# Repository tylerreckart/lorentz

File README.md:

# LORENTZ
An all-analog topology complex oscillator inspired by Don Buchla’s 259. Sized for Eurorack (28 HP).  

![LORENTZ REV-A front panels, off-white and black][image-1]

## Overview
Two oscillators, a modulation oscillator and a principal oscillator:
- **Modulation oscillator:** coarse dial (about 0.1 Hz to 1.6 kHz; the -3 to +3 engraving is a set of landmarks), FREQ CV input, MOD OUTS (two waveforms).
- **Principal oscillator:** coarse tuning dial (-3 to +3 octaves), FINE, PITCH (1 V/oct) and EXP CV inputs, PRINC OUTS (two waveforms).
- **Modulation:** INDEX and AM, with an EXP/LIN toggle.
- **Timbre:** TIMBRE (wavefolder) and SYMM, with the FINAL output.
- **Waveshaping:** SHAPE (triangle to square), with a WAVE output.

Full operating and calibration instructions are in the [manual](MANUAL.md) ([PDF](docs/LORENTZ_REV-A_Manual.pdf)).
## Front panel
- Eurorack 3U x 28 HP: **141.9 x 128.5 mm**, square corners.
- **2.0 mm** 5052 (or 6061) aluminium.
- **39 holes + 4 rail slots.**

| Feature         | Qty | Dia (mm)                                 | Part                                   |
| --------------- | --- | ---------------------------------------- | -------------------------------------- |
| Pot bushings    | 8   | 7.3                                      | Alpha 9 mm x6, Alpha RV16 x2 (M7x0.75) |
| Jacks           | 13  | 6.3                                      | Thonkiconn PJ398SM (M6)                |
| Toggle          | 1   | 5.2                                      | Dailywell 2MD1T1B1M2QES (10-48 UNS)    |
| LEDs            | 11  | 3.2                                      | 3 mm LED, lens flush (9 red, 2 amber)  |
| Standoff screws | 6   | 3.4 thru + 90° countersink Ø6.0 on front | M3x6 DIN 965 / ISO 7046 countersunk    |
| Rail slots      | 4   | 5.6 x 3.2 stadium                        | M3 rail screws                         |

Colourways:

| Version   | Base           | Ink                 | Accents                    |
| --------- | -------------- | ------------------- | -------------------------- |
| Off-white | \#E9E6DC matte | \#2A1404 dark brown | red #D8302A, amber #ECB731 |
| Black     | \#2C2C2C matte | white               | red #D8302A, amber #ECB731 |

Full details, including countersink depth and print registration, are in `panel/<colour>/PANEL_FAB_SPEC.md`.
## Fabrication
**PCBs.** Zip and upload each gerber folder separately:
- `control_board/gerbers/` (12 files: 4 copper, mask, silk, edge, drill + map, job)
- `circuit_board/gerbers/` (same)
**Panel.**
1. Cut and drill from `panel/<colour>/panel_REV-A_cut.dxf` (mm, origin bottom-left; layers `CUT` and `CSK_FRONT_6.0x90`). `panel_REV-A_cut.svg` is the same geometry.
2. Countersink the six standoff holes first, then UV-print.
3. Print from `panel/<colour>/LORENTZ_REV-A_print_<colour>_outlined.svg`. Register to the hole centers in `panel_REV-A_holes.csv` within ±0.2 mm.
Ask the fab for a color proof against the base color.
## Bill of materials
See `bom/`. `LORENTZ_REV-A_BOM.csv` lists suppliers, part numbers and prices (`need` is the count for one build; `qty` includes spares). The `*_bom_from_sch.csv` files are fresh exports from the schematics.
## Calibration
There are three trimmers on the rear of the circuit board: RV4 (1 V/oct scale), RV5 (high-frequency tracking) and RV11 (SHAPE CV offset null). See section 12 of the [manual](MANUAL.md).
## Repository layout
- `MANUAL.md`: user manual (source). `docs/LORENTZ_REV-A_Manual.pdf` is the printable version; `images/manual/` holds its figures.
- `control_board/`, `circuit_board/`: KiCad projects, schematic PDFs, pick-and-place files and `gerbers/`.
- `panel/<colour>/`: panel cut files, print artwork and `PANEL_FAB_SPEC.md`.
- `bom/`: bills of materials.
- `images/`: panel renders.
## License
Apache 2.0

[image-1]:	images/LORENTZ_REV-A_offwhite.png

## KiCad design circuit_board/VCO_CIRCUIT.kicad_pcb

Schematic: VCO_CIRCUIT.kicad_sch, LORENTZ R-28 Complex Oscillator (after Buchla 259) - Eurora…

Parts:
C1, C2: 47u; CP_Radial_D5.0mm_P2.00mm
C3, C4, C6, C7, C8, C9, C10, C11, C12, C13, C17, C18, C19, C20, C23, C24, C26, C27, C28, C29, C30, C31, C36, C37, C38, C39, C44, C45, C46, C47, C48, C49: 100n; C_Disc_D3.0mm_W2.0mm_P2.50mm
C5: 10u; CP_Radial_D5.0mm_P2.00mm
C14, C21, C33, C35, C41, C43: 47p; C_Disc_D3.0mm_W2.0mm_P2.50mm
C15, C22, C32, C34, C40, C42: 100p; C_Disc_D3.0mm_W2.0mm_P2.50mm
C16: 10n C0G; C_Disc_D3.0mm_W2.0mm_P2.50mm
C25: 330p C0G; C_Disc_D3.0mm_W2.0mm_P2.50mm
D1, D2: 1N5817; D_DO-41_SOD81_P10.16mm_Horizontal
D3: BZX79C5V1; D_DO-35_SOD27_P2.54mm_Vertical_KathodeUp
D4, D5, D6, D7, D8, D9, D10, D11, D12, D13, D14, D15, D16, D17, D18, D19, D20, D21, D22, D24, D26, D28, D30, D32, D34, D36, D38, D42: 1N4148; D_DO-35_SOD27_P2.54mm_Vertical_KathodeUp
D45: BZX79B6V8; D_DO-35_SOD27_P2.54mm_Vertical_KathodeUp
J1: Eurorack 10p; IDC-Header_2x05_P2.54mm_Vertical__J1
J20, J21: B2B 2x15 female; PinSocket_2x15_P2.54mm_Vertical
Q1, Q2, Q3, Q4: BC557B; TO-92_Inline
R1, R2: 10; R_Axial_DIN0204_L3.6mm_D1.6mm_P2.54mm_Vertical
R3, R21, R41, R43, R44, R46, R50, R119, R120, R121, R122, R123, R124, R125, R126, R128: 2.2k; R_Axial_DIN0204_L3.6mm_D1.6mm_P2.54mm_Vertical
R4: 187k; R_Axial_DIN0204_L3.6mm_D1.6mm_P2.54mm_Vertical
R5, R31, R32: 110k; R_Axial_DIN0204_L3.6mm_D1.6mm_P2.54mm_Vertical
R6, R33: 2k +3300ppm; R_Axial_DIN0204_L3.6mm_D1.6mm_P2.54mm_Vertical
R7, R34: 47; R_Axial_DIN0204_L3.6mm_D1.6mm_P2.54mm_Vertical
R8: 3.92Meg; R_Axial_DIN0204_L3.6mm_D1.6mm_P2.54mm_Vertical
R9, R36: 6.8k; R_Axial_DIN0204_L3.6mm_D1.6mm_P2.54mm_Vertical
R10: 4.7Meg; R_Axial_DIN0204_L3.6mm_D1.6mm_P2.54mm_Vertical
R12, R13, R67, R68, R78, R79, R95, R96, R110, R111: 220; R_Axial_DIN0204_L3.6mm_D1.6mm_P2.54mm_Vertical
R14, R129, R130: 4.7k; R_Axial_DIN0204_L3.6mm_D1.6mm_P2.54mm_Vertical
R15, R17, R24, R25, R45, R47, R64, R65, R104, R118: 1k; R_Axial_DIN0204_L3.6mm_D1.6mm_P2.54mm_Vertical
R16, R18: 470; R_Axial_DIN0204_L3.6mm_D1.6mm_P2.54mm_Vertical
R19, R48: 47k; R_Axial_DIN0204_L3.6mm_D1.6mm_P2.54mm_Vertical
R20, R74, R103: 30k; R_Axial_DIN0204_L3.6mm_D1.6mm_P2.54mm_Vertical
R22, R60: 5.1k; R_Axial_DIN0204_L3.6mm_D1.6mm_P2.54mm_Vertical
R23, R38, R52, R55, R56, R57, R59, R61, R62, R63, R72, R84, R88, R89, R90, R91, R92, R93, R101, R105, R107, R114: 10k; R_Axial_DIN0204_L3.6mm_D1.6mm_P2.54mm_Vertical
R26: 442k; R_Axial_DIN0204_L3.6mm_D1.6mm_P2.54mm_Vertical
R27, R28: 220k; R_Axial_DIN0204_L3.6mm_D1.6mm_P2.54mm_Vertical
R29: 3.3Meg; R_Axial_DIN0204_L3.6mm_D1.6mm_P2.54mm_Vertical
R30, R71, R73, R75, R76, R83, R85, R94, R98, R100, R102, R109, R113, R115, R117, R131: 100k; R_Axial_DIN0204_L3.6mm_D1.6mm_P2.54mm_Vertical
R35: 1.5Meg; R_Axial_DIN0204_L3.6mm_D1.6mm_P2.54mm_Vertical
R37: 1Meg; R_Axial_DIN0204_L3.6mm_D1.6mm_P2.54mm_Vertical
R39: 22k; R_Axial_DIN0204_L3.6mm_D1.6mm_P2.54mm_Vertical
R40, R42: 18k; R_Axial_DIN0204_L3.6mm_D1.6mm_P2.54mm_Vertical
R49, R66, R77: 68k; R_Axial_DIN0204_L3.6mm_D1.6mm_P2.54mm_Vertical
R51: 4.3k; R_Axial_DIN0204_L3.6mm_D1.6mm_P2.54mm_Vertical
R53: 91k; R_Axial_DIN0204_L3.6mm_D1.6mm_P2.54mm_Vertical
R54: 39k; R_Axial_DIN0204_L3.6mm_D1.6mm_P2.54mm_Vertical
R58: 20k; R_Axial_DIN0204_L3.6mm_D1.6mm_P2.54mm_Vertical
R69, R80, R99: 200k; R_Axial_DIN0204_L3.6mm_D1.6mm_P2.54mm_Vertical
R70, R81: 330k; R_Axial_DIN0204_L3.6mm_D1.6mm_P2.54mm_Vertical
R82: 680k; R_Axial_DIN0204_L3.6mm_D1.6mm_P2.54mm_Vertical
R86, R133: 470k; R_Axial_DIN0204_L3.6mm_D1.6mm_P2.54mm_Vertical
R87: 25.5k; R_Axial_DIN0204_L3.6mm_D1.6mm_P2.54mm_Vertical
R97: 240k; R_Axial_DIN0204_L3.6mm_D1.6mm_P2.54mm_Vertical
R106, R108: 4.99k; R_Axial_DIN0204_L3.6mm_D1.6mm_P2.54mm_Vertical
R112: 143k; R_Axial_DIN0204_L3.6mm_D1.6mm_P2.54mm_Vertical
R116: 34k; R_Axial_DIN0204_L3.6mm_D1.6mm_P2.54mm_Vertical
R132: 42.2k; R_Axial_DIN0204_L3.6mm_D1.6mm_P2.54mm_Vertical
RV4: 20k; Potentiometer_Bourns_3296W_Vertical
RV5: 10k; Potentiometer_Bourns_3296W_Vertical
RV11: 100k; Potentiometer_Bourns_3296W_Vertical
U1: THAT320P14-U; DIP-14_W7.62mm_Socket
U2: LM319N/NOPB; DIP-14_W7.62mm_Socket
U3, U10, U13: LM13700N/NOPB; DIP-16_W7.62mm_Socket
U4, U6: CD4053BE; DIP-16_W7.62mm_Socket
U5, U7, U8, U9, U11, U12, U14, U15, U16: TL074; DIP-14_W7.62mm_Socket

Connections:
/+12V: C1.1, C3.1, C6.1, C8.1, C10.1, C12.1, C17.1, C19.1, C23.1, C26.1, C28.1, C30.1, C36.1, C38.1, C44.1, C46.1, C48.1, J20.2, J21.2, R1.2, R15.1, R21.1, R27.1, R39.1, R44.1, R50.1, R53.1, R82.1, R97.1, RV11.1, U2.11 (V+), U3.11 (V+), U4.16 (VDD), U5.4 (V+), U6.16 (VDD), U7.4 (V+), U8.4 (V+), U9.4 (V+), U10.11 (V+), U11.4 (V+), U12.4 (V+), U13.11 (V+), U14.4 (V+), U15.4 (V+), U16.4 (V+)
/+12V_D: D1.1 (K), R1.1
/+12V_IN: D1.2 (A), J1.9, J1.10
/-12V: C2.2, C4.1, C7.1, C9.1, C13.1, C20.1, C24.1, C27.1, C29.1, C31.1, C37.1, C39.1, C45.1, C47.1, C49.1, J20.3, J21.3, R2.1, R3.1, R8.2, R17.1, R28.1, R35.2, R38.2, R46.1, RV11.3, U2.6 (V-), U3.6 (V-), U5.11 (V-), U7.11 (V-), U8.11 (V-), U9.11 (V-), U10.6 (V-), U11.11 (V-), U12.11 (V-), U13.6 (V-), U14.11 (V-), U15.11 (V-), U16.11 (V-)
/-12V_D: D2.2 (A), R2.2
/-12V_IN: D2.1 (K), J1.1, J1.2
/AM_CV_J: J20.8, R99.1
/AM_IABC: Q3.1 (C), U13.1
/AM_IN: R94.2, R95.1, U13.3 (+)
/AM_INM: R96.1, U13.4 (-)
/AM_IV: C41.1, R103.1, U12.2 (-), U13.5
/AM_W: J20.4, U15.3 (+)
/F1_CL: D15.2 (A), D16.1 (K), R88.2, U9.10 (+)
/F1_N: R89.2, R90.1, U9.9 (-)
/F1_OUT: R90.2, R91.1, R92.1, U9.8
/F2_CL: D17.2 (A), D20.1 (K), R91.2, U9.12 (+)
/F2_D1: D17.1 (K), D18.2 (A)
/F2_D2: D19.1 (K), D20.2 (A)
/F2_N: R92.2, R93.1, U9.13 (-)
/F2_OUT: R93.2, R94.1, U9.14, U14.12 (+)
/FMI_CV_J: J20.29, R70.1
/FMI_W: J20.22, R69.1
/FM_EXP: J21.8, R32.1, R75.1
/FM_IABC: Q1.1 (C), U10.1
/FM_IN: R66.2, R67.1, U10.3 (+)
/FM_INM: R68.1, U10.4 (-)
/FM_IV: C33.1, R74.1, U9.2 (-), U10.5
/FM_LIN: J20.27, R54.1, R76.1
/FM_MOD: C33.2, J21.1, R74.2, U9.1
/GND: C1.2, C2.1, C3.2, C4.2, C5.1, C6.2, C7.2, C8.2, C9.2, C10.2, C11.2, C12.2, C13.2, C16.2, C17.2, C18.2, C19.2, C20.2, C23.2, C24.2, C25.2, C26.2, C27.2, C28.2, C29.2, C30.2, C31.2, C36.2, C37.2, C38.2, C39.2, C44.2, C45.2, C46.2, C47.2, C48.2, C49.2, D3.1 (K), D15.1 (K), D16.2 (A), D18.1 (K), D19.2 (A), D24.2 (A), D26.2 (A), D28.2 (A), D30.2 (A), D32.2 (A), D34.2 (A), D36.2 (A), D38.2 (A), D42.2 (A), J1.3, J1.4, J1.5, J1.6, J1.7, J1.8, J20.5, J20.10, J20.15, J20.20, J20.25, J20.30, J21.5, J21.10, J21.15, J21.20, J21.25, J21.29, J21.30, R12.2, R13.2, R16.2, R18.2, R23.2, R41.2, R42.2, R43.2, R45.2, R47.2, R52.2, R62.2, R63.2, R67.2, R68.2, R71.2, R72.2, R75.2, R76.2, R78.2, R79.2, R83.2, R84.2, R95.2, R96.2, R100.2, R101.2, R106.2, R110.2, R111.2, R113.2, R114.2, RV5.3, U1.2 (Q1_B), U1.4 (SUB), U1.6 (Q3_B), U1.11 (SUB), U2.3 (GND), U2.5 (-), U2.8 (GND), U2.10 (-), U3.7, U4.1 (Y1), U4.2 (Y0), U4.3 (Z1), U4.5 (Z0), U4.6 (Inh), U4.8 (VSS), U4.9 (C), U4.10 (B), U5.3 (+), U5.5 (+), U6.6 (Inh), U6.8 (VSS), U7.3 (+), U7.5 (+), U8.3 (+), U8.5 (+), U8.10 (+), U8.13 (-), U9.3 (+), U9.5 (+), U10.7, U10.10, U11.3 (+), U11.5 (+), U11.10 (+), U11.12 (+), U12.3 (+), U12.5 (+), U12.12 (+), U13.7, U13.10, U16.5 (+), U16.12 (+)
/LD1: R119.1, U14.1, U14.2 (-)
/LD1_A: D24.1 (K), J20.7, R119.2
/LD2: R107.1, R117.1, U14.6 (-), U14.7
/LD3: R120.1, U14.8, U14.9 (-)
/LD3_A: D26.1 (K), J21.28, R120.2
/LD4: R121.1, U14.13 (-), U14.14
/LD4_A: D28.1 (K), J21.21, R121.2
/LD5: R98.1, R122.1, U15.1, U15.2 (-)
/LD5_A: D30.1 (K), J20.11, R122.2
/LD6: R123.1, U15.6 (-), U15.7
/LD6_A: D32.1 (K), J20.14, R123.2
/LD7: R124.1, U15.8, U15.9 (-)
/LD7_A: D34.1 (K), J20.18, R124.2
/LD8: R125.1, U15.13 (-), U15.14
/LD8_A: D36.1 (K), J21.17, R125.2
/LD9: R126.1, U16.1, U16.2 (-)
/LD9_A: D38.1 (K), J21.13, R126.2
/LD11: R128.1, U16.8, U16.9 (-)
/LD11_A: D42.1 (K), J21.7, R128.2
/MAIN: C41.2, R103.2, R104.1, U12.1, U16.10 (+)
/MAIN_J: J21.4, R104.2
/MODE_EXP: J21.9, R129.1
/MODE_EXP_A: J20.21, R129.2
/MODE_LIN: J20.28, R130.1
/MODE_LIN_A: J21.11, R130.2
/M_BASE: R7.2, U1.13 (Q2_B)
/M_CAP: C16.1, U3.5, U5.12 (+)
/M_CK1: D4.1 (K), D5.2 (A)
/M_CK2: D6.1 (K), D7.2 (A)
/M_CRS_W: J20.12, R4.1
/M_CV_J: J20.9, R5.1
/M_E: R9.2, U1.3 (Q1_E), U1.12 (Q2_E)
/M_H: R19.2, R20.2, U2.4 (+)
/M_IABC: U1.14 (Q2_C), U3.1
/M_OM: R13.1, R14.2, U3.4 (-)
/M_OP: R12.1, U3.3 (+)
/M_REF: C15.1, R8.1, U1.1 (Q1_C), U5.6 (-)
/M_REFO: C15.2, R9.1, R10.1, U5.7
/M_S: R21.2, U2.12, U4.11 (A)
/M_SQN: R22.2, R23.1, U5.9 (-)
/M_SQRO: R22.1, R25.1, U5.8, U15.10 (+)
/M_SQR_J: J20.17, R25.2
/M_SUM: C14.1, D4.2 (A), D7.1 (K), R4.2, R5.2, R6.1, R10.2, U5.2 (-)
/M_SUMOUT: C14.2, D5.1 (K), D6.2 (A), R6.2, R7.1, U5.1
/M_TRI: J20.6, R19.1, R24.1, R66.1, U5.13 (-), U5.14, U14.3 (+), U15.5 (+)
/M_TRI_J: J20.13, R24.2
/M_VRN: R17.2, R18.1, U4.12 (X0)
/M_VRP: R15.2, R16.1, U4.13 (X1)
/M_VSW: R14.1, R20.1, U4.14 (X), U5.10 (+)
/P_BASE: R34.2, U1.9 (Q4_B)
/P_BIAS: R39.2, U3.15 (DIODE_BIAS)
/P_CAP: C25.1, U3.10, U3.12
/P_CK1: D8.1 (K), D9.2 (A)
/P_CK2: D10.1 (K), D11.2 (A)
/P_CRS_W: J21.18, R26.1
/P_CV_J: J21.19, R31.1
/P_E: R36.2, U1.5 (Q3_E), U1.10 (Q4_E)
/P_FH: J21.23, R27.2
/P_FINE_W: J21.24, R29.1
/P_FL: J21.26, R28.2
/P_H: R48.2, R49.2, U2.9 (+)
/P_HFW: R37.1, RV5.2
/P_IABC: U1.8 (Q4_C), U3.16
/P_NTH: R60.2, U6.2 (Y0)
/P_NTO: R59.2, R60.1, U8.8
/P_NX: R57.2, U6.13 (X1), U8.7
/P_NXN: R56.2, R57.1, U8.6 (-)
/P_OM: R42.1, R43.1, U3.13 (-)
/P_OP: R40.2, R41.1, U3.14 (+)
/P_REF: C22.1, R35.1, U1.7 (Q3_C), U7.6 (-)
/P_REFO: C22.2, R36.1, RV5.1, U7.7
/P_S: R50.2, U2.7, U6.9 (C), U6.11 (A)
/P_SG: D12.1 (K), R63.1, U6.10 (B)
/P_SGO: D12.2 (A), U8.14
/P_SQN: R51.2, R52.1, U7.9 (-)
/P_SQRO: J20.23, R51.1, R65.1, R105.1, U7.8, U16.3 (+)
/P_SQR_J: J21.12, R65.2
/P_SUM: C21.1, D8.2 (A), D11.1 (K), R26.2, R29.2, R31.2, R32.2, R33.1, R37.2, RV4.2, RV4.3, U7.2 (-)
/P_SUMOUT: C21.2, D9.1 (K), D10.2 (A), R33.2, R34.1, U7.1
/P_TH: R61.2, R62.1, U6.1 (Y1)
/P_TIN: R58.2, R59.1, U8.9 (-)
/P_TRI: J20.24, R58.1, R61.1, R64.1, R77.1, U7.13 (-), U7.14, U14.10 (+), U15.12 (+)
/P_TRIB: R38.1, U3.9, U7.12 (+)
/P_TRI_J: J21.16, R64.2
/P_TS: R48.1, U6.15 (Y)
/P_VOCT_J: J21.14, R30.1
/P_VRN: R46.2, R47.1, U6.5 (Z0)
/P_VRP: R44.2, R45.1, U6.3 (Z1)
/P_VSW: R49.1, U6.4 (Z), U7.10 (+)
/P_VT: R30.2, RV4.1
/P_X: R55.2, R56.1, U6.12 (X0), U8.1, U8.12 (+)
/P_XN: R53.2, R54.2, R55.1, U8.2 (-)
/P_XS: R40.1, U6.14 (X)
/SC_IN: R109.2, R110.1, U13.13 (-)
/SC_INP: R111.1, R133.2, U13.14 (+)
/SC_IV: C43.1, R116.1, U12.13 (-), U13.12
/SC_TRIM: R133.1, RV11.2
/SC_V: C43.2, R116.2, R132.1, U12.14
/SD_M: R107.2, R108.1, U12.9 (-)
/SD_OUT: R108.2, R109.1, U12.8
/SD_P: R105.2, R106.1, U12.10 (+)
/SH_CV_J: J21.6, R112.1
/SH_IABC: Q4.1 (C), U13.16
/SH_J: J20.16, R118.2
/SH_OUT: R118.1, R131.1, U12.7
/SH_SUM: R117.2, R131.2, R132.2, U12.6 (-)
/SH_W: J20.26, U14.5 (+)
/SYM_W: J20.1, R86.1
/TB_CV_J: J21.27, R81.1
/TB_DRV: C35.2, R87.2, R88.1, R89.1, U9.7
/TB_IABC: Q2.1 (C), U10.16
/TB_IN: R77.2, R78.1, U10.14 (+)
/TB_INM: R79.1, U10.13 (-)
/TB_IV: C35.1, R86.2, R87.1, U9.6 (-), U10.12
/TB_W: J21.22, R80.1
/U16B_TIE: U16.6 (-), U16.7
/U16D_TIE: U16.13 (-), U16.14
/VEE: C5.2, C11.1, C18.1, D3.2 (A), R3.2, U4.7 (VEE), U6.7 (VEE)
/VI1_B: D13.2 (A), Q1.2 (B), R71.1
/VI1_E: C32.1, Q1.3 (E), R72.1, R73.1
/VI1_N: C32.2, R69.2, R70.2, R73.2, U11.2 (-)
/VI1_O: D13.1 (K), U11.1
/VI2_B: D14.2 (A), Q2.2 (B), R83.1
/VI2_E: C34.1, Q2.3 (E), R84.1, R85.1
/VI2_N: C34.2, R80.2, R81.2, R82.2, R85.2, U11.6 (-)
/VI2_O: D14.1 (K), U11.7
/VI3_B: D21.2 (A), Q3.2 (B), R100.1
/VI3_E: C40.1, Q3.3 (E), R101.1, R102.1
/VI3_N: C40.2, R97.2, R98.2, R99.2, R102.2, U11.9 (-)
/VI3_O: D21.1 (K), U11.8
/VI4_B: D22.2 (A), Q4.2 (B), R113.1
/VI4_E: C42.1, Q4.3 (E), R114.1, R115.1
/VI4_N: C42.2, D45.1 (K), R112.2, R115.2, U11.13 (-)
/VI4_O: D22.1 (K), D45.2 (A), U11.14

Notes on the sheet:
POWER: Eurorack 10-pin, reverse protection, decoupling
MODULATION OSCILLATOR (THAT320 expo + tempco, LM13700 core, LM319/CD4053 switching)
PRINCIPAL OSCILLATOR (1V/oct, HF comp, through-zero linear FM core)
FM INDEX VCA + LIN/EXP
TIMBRE: VCA drive + symmetry + 2-stage diode wavefolder
AM VCA (+AM CV), SHAPE morph (+SHAPE CV OTA), outputs
LED DRIVERS: TL074 followers, 2.2k limit, 1N4148 reverse clamp

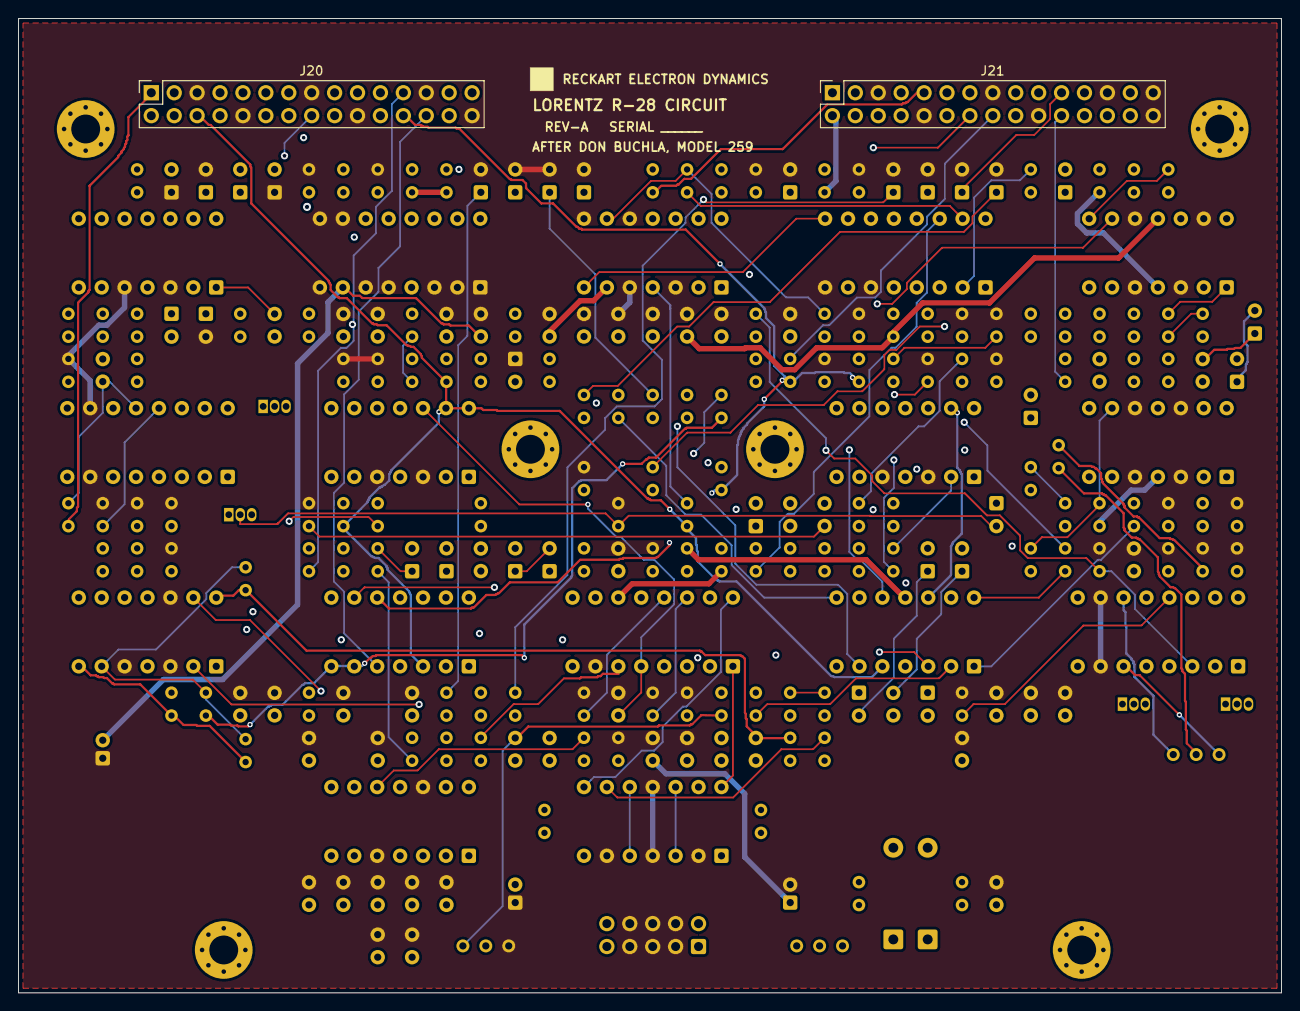
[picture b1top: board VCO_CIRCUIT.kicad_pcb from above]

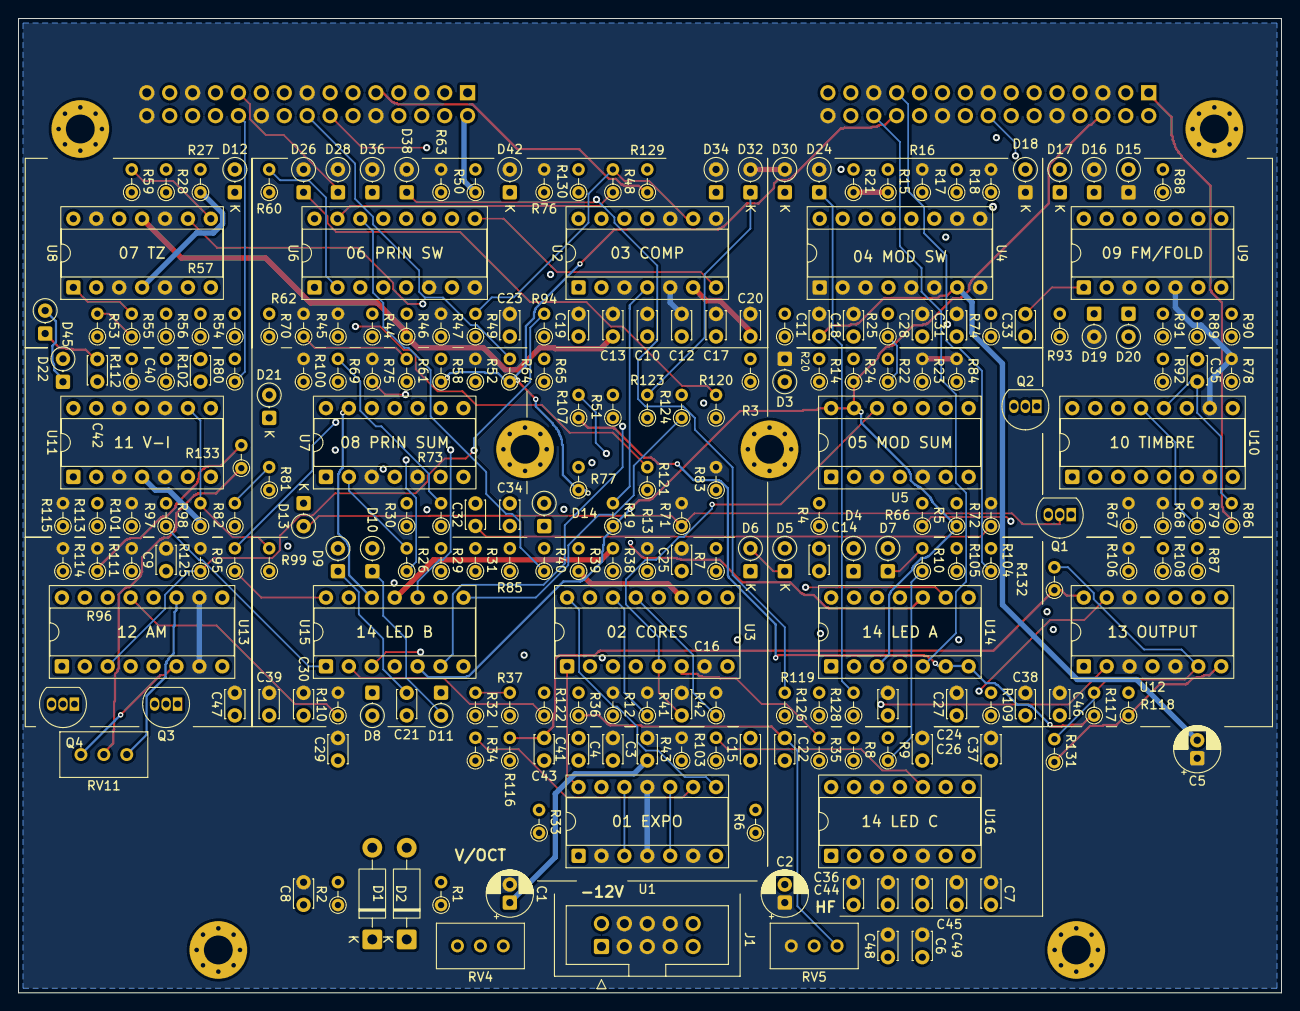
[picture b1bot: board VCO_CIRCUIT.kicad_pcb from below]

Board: 4 copper layers, 140.0 x 108.0 mm, 244 parts (236 on the bottom side), 164 nets.

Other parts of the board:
H1, H2, H3, H4, H5, H6: M3 standoff; MountingHole_3.2mm_M3_Pad_Via

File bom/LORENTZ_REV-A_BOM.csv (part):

ref,qty,desc,mfr_pn,supplier,supplier_pn,unit_price,ext,stock,URL,need,note
"R1,R2",10,Resistor 10 1% 0.25W metal film axial,MFR-25FBF52-10R,Mouser,603-MFR-25FBF52-10R,0.1,1.0,stock unverified (site blocks automated access),https://www.mouser.com/ProductDetail/603-MFR-25FBF52-10R,2,8 spare
"R3,R21,R41,R43,R44,R46,R50,R119-R126,R128",20,Resistor 2.2k 1% 0.25W metal film axial,MFR-25FBF52-2K2,Mouser,603-MFR-25FBF52-2K2,0.06,1.2,stock unverified (site blocks automated access),https://www.mouser.com/ProductDetail/603-MFR-25FBF52-2K2,16,4 spare
R4,10,Resistor 187k 1% 0.25W metal film axial,MFR-25FBF52-187K,Mouser,603-MFR-25FBF52-187K,0.1,1.0,stock unverified (site blocks automated access),https://www.mouser.com/ProductDetail/603-MFR-25FBF52-187K,1,9 spare
R26,10,Resistor 442k 1% 0.25W metal film axial,MFR-25FBF52-442K,Mouser,603-MFR-25FBF52-442K,0.1,1.0,stock unverified (site blocks automated access),https://www.mouser.com/ProductDetail/603-MFR-25FBF52-442K,1,9 spare
"R5,R31,R32",10,Resistor 110k 1% 0.25W metal film axial,MFR-25FBF52-110K,Mouser,603-MFR-25FBF52-110K,0.1,1.0,stock unverified (site blocks automated access),https://www.mouser.com/ProductDetail/603-MFR-25FBF52-110K,3,7 spare
"R7,R34",10,Resistor 47 1% 0.25W metal film axial,MFR-25FBF52-47R,Mouser,603-MFR-25FBF52-47R,0.1,1.0,stock unverified (site blocks automated access),https://www.mouser.com/ProductDetail/603-MFR-25FBF52-47R,2,8 spare
R8,10,Resistor 3.92M 1% 0.25W metal film axial,MFR-25FBF52-3M92,Mouser,603-MFR-25FBF52-3M92,0.1,1.0,stock unverified (site blocks automated access),https://www.mouser.com/ProductDetail/603-MFR-25FBF52-3M92,1,9 spare
R35,10,Resistor 1.5M 1% 0.25W metal film axial,MFR-25FBF52-1M5,Mouser,603-MFR-25FBF52-1M5,0.1,1.0,stock unverified (site blocks automated access),https://www.mouser.com/ProductDetail/603-MFR-25FBF52-1M5,1,9 spare
"R9,R36",10,Resistor 6.8k 1% 0.25W metal film axial,MFR-25FBF52-6K8,Mouser,603-MFR-25FBF52-6K8,0.1,1.0,stock unverified (site blocks automated access),https://www.mouser.com/ProductDetail/603-MFR-25FBF52-6K8,2,8 spare
R10,10,Resistor 4.7M 1% 0.25W metal film axial,MFR-25FBF52-4M7,Mouser,603-MFR-25FBF52-4M7,0.1,1.0,stock unverified (site blocks automated access),https://www.mouser.com/ProductDetail/603-MFR-25FBF52-4M7,1,9 spare
"R23,R38,R52,R55-R57,R59,R61-R63,R72,R84,R88-R93,R101,R105,R107,R114",30,Resistor 10k 1% 0.25W metal film axial,MFR-25FBF52-10K,Mouser,603-MFR-25FBF52-10K,0.06,1.8,stock unverified (site blocks automated access),https://www.mouser.com/ProductDetail/603-MFR-25FBF52-10K,22,8 spare
"R12,R13,R67,R68,R78,R79,R95,R96,R110,R111",10,Resistor 220 1% 0.25W metal film axial,MFR-25FBF52-220R,Mouser,603-MFR-25FBF52-220R,0.1,1.0,stock unverified (site blocks automated access),https://www.mouser.com/ProductDetail/603-MFR-25FBF52-220R,10,
"R14,R129,R130",10,Resistor 4.7k 1% 0.25W metal film axial,MFR-25FBF52-4K7,Mouser,603-MFR-25FBF52-4K7,0.1,1.0,stock unverified (site blocks automated access),https://www.mouser.com/ProductDetail/603-MFR-25FBF52-4K7,3,7 spare
"R15,R17,R24,R25,R45,R47,R64,R65,R104,R118",10,Resistor 1k 1% 0.25W metal film axial,MFR-25FBF52-1K,Mouser,603-MFR-25FBF52-1K,0.1,1.0,stock unverified (site blocks automated access),https://www.mouser.com/ProductDetail/603-MFR-25FBF52-1K,10,
"R16,R18",10,Resistor 470 1% 0.25W metal film axial,MFR-25FBF52-470R,Mouser,603-MFR-25FBF52-470R,0.1,1.0,stock unverified (site blocks automated access),https://www.mouser.com/ProductDetail/603-MFR-25FBF52-470R,2,8 spare
"R19,R48",10,Resistor 47k 1% 0.25W metal film axial,MFR-25FBF52-47K,Mouser,603-MFR-25FBF52-47K,0.1,1.0,stock unverified (site blocks automated access),https://www.mouser.com/ProductDetail/603-MFR-25FBF52-47K,2,8 spare
"R20,R74,R103",10,Resistor 30k 1% 0.25W metal film axial,MFR-25FBF52-30K,Mouser,603-MFR-25FBF52-30K,0.1,1.0,stock unverified (site blocks automated access),https://www.mouser.com/ProductDetail/603-MFR-25FBF52-30K,3,7 spare
"R22,R60",10,Resistor 5.1k 1% 0.25W metal film axial,MFR-25FBF52-5K1,Mouser,603-MFR-25FBF52-5K1,0.1,1.0,stock unverified (site blocks automated access),https://www.mouser.com/ProductDetail/603-MFR-25FBF52-5K1,2,8 spare
"R27,R28",10,Resistor 220k 1% 0.25W metal film axial,MFR-25FBF52-220K,Mouser,603-MFR-25FBF52-220K,0.1,1.0,stock unverified (site blocks automated access),https://www.mouser.com/ProductDetail/603-MFR-25FBF52-220K,2,8 spare
R29,10,Resistor 3.3M 1% 0.25W metal film axial,MFR-25FBF52-3M3,Mouser,603-MFR-25FBF52-3M3,0.1,1.0,stock unverified (site blocks automated access),https://www.mouser.com/ProductDetail/603-MFR-25FBF52-3M3,1,9 spare
"R30,R71,R73,R75,R76,R83,R85,R94,R98,R100,R102,R109,R113,R115,R117,R131",20,Resistor 100k 1% 0.25W metal film axial,MFR-25FBF52-100K,Mouser,603-MFR-25FBF52-100K,0.06,1.2,stock unverified (site blocks automated access),https://www.mouser.com/ProductDetail/603-MFR-25FBF52-100K,16,4 spare
"R106,R108",10,Resistor 4.99k 1% 0.25W metal film axial,MFR-25FBF52-4K99,Mouser,603-MFR-25FBF52-4K99,0.1,1.0,stock unverified (site blocks automated access),https://www.mouser.com/ProductDetail/603-MFR-25FBF52-4K99,2,8 spare
R132,10,Resistor 42.2k 1% 0.25W metal film axial,MFR-25FBF52-42K2,Mouser,603-MFR-25FBF52-42K2,0.1,1.0,stock unverified (site blocks automated access),https://www.mouser.com/ProductDetail/603-MFR-25FBF52-42K2,1,9 spare
R37,10,Resistor 1M 1% 0.25W metal film axial,MFR-25FBF52-1M,Mouser,603-MFR-25FBF52-1M,0.1,1.0,stock unverified (site blocks automated access),https://www.mouser.com/ProductDetail/603-MFR-25FBF52-1M,1,9 spare
R39,10,Resistor 22k 1% 0.25W metal film axial,MFR-25FBF52-22K,Mouser,603-MFR-25FBF52-22K,0.1,1.0,stock unverified (site blocks automated access),https://www.mouser.com/ProductDetail/603-MFR-25FBF52-22K,1,9 spare
"R40,R42",10,Resistor 18k 1% 0.25W metal film axial,MFR-25FBF52-18K,Mouser,603-MFR-25FBF52-18K,0.1,1.0,stock unverified (site blocks automated access),https://www.mouser.com/ProductDetail/603-MFR-25FBF52-18K,2,8 spare
"R49,R66,R77",10,Resistor 68k 1% 0.25W metal film axial,MFR-25FBF52-68K,Mouser,603-MFR-25FBF52-68K,0.1,1.0,stock unverified (site blocks automated access),https://www.mouser.com/ProductDetail/603-MFR-25FBF52-68K,3,7 spare
R51,10,Resistor 4.3k 1% 0.25W metal film axial,MFR-25FBF52-4K3,Mouser,603-MFR-25FBF52-4K3,0.1,1.0,stock unverified (site blocks automated access),https://www.mouser.com/ProductDetail/603-MFR-25FBF52-4K3,1,9 spare
R53,10,Resistor 91k 1% 0.25W metal film axial,MFR-25FBF52-91K,Mouser,603-MFR-25FBF52-91K,0.1,1.0,stock unverified (site blocks automated access),https://www.mouser.com/ProductDetail/603-MFR-25FBF52-91K,1,9 spare
R54,10,Resistor 39k 1% 0.25W metal film axial,MFR-25FBF52-39K,Mouser,603-MFR-25FBF52-39K,0.1,1.0,stock unverified (site blocks automated access),https://www.mouser.com/ProductDetail/603-MFR-25FBF52-39K,1,9 spare
R58,10,Resistor 20k 1% 0.25W metal film axial,MFR-25FBF52-20K,Mouser,603-MFR-25FBF52-20K,0.1,1.0,stock unverified (site blocks automated access),https://www.mouser.com/ProductDetail/603-MFR-25FBF52-20K,1,9 spare
"R69,R80,R99",10,Resistor 200k 1% 0.25W metal film axial,MFR-25FBF52-200K,Mouser,603-MFR-25FBF52-200K,0.1,1.0,stock unverified (site blocks automated access),https://www.mouser.com/ProductDetail/603-MFR-25FBF52-200K,3,7 spare
"R70,R81",10,Resistor 330k 1% 0.25W metal film axial,MFR-25FBF52-330K,Mouser,603-MFR-25FBF52-330K,0.1,1.0,stock unverified (site blocks automated access),https://www.mouser.com/ProductDetail/603-MFR-25FBF52-330K,2,8 spare
R82,10,Resistor 680k 1% 0.25W metal film axial,MFR-25FBF52-680K,Mouser,603-MFR-25FBF52-680K,0.1,1.0,stock unverified (site blocks automated access),https://www.mouser.com/ProductDetail/603-MFR-25FBF52-680K,1,9 spare
"R86,R133",10,Resistor 470k 1% 0.25W metal film axial,MFR-25FBF52-470K,Mouser,603-MFR-25FBF52-470K,0.1,1.0,stock unverified (site blocks automated access),https://www.mouser.com/ProductDetail/603-MFR-25FBF52-470K,2,8 spare
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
